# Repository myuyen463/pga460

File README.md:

# PGA460

Embedded platform for interfacing with Mega 2560 and multiple transducers

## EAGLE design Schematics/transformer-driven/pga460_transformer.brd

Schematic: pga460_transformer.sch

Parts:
5V/GND: FE05-2
B1: ARDUINO_MEGA_R3FULL; ARDUINO_MEGA_NO_SILK
C1, C2, C3, C6, C9, C12, C15, C16, C19: 0.1uF; C0805
C4, C10, C17: 100uF; C0805
C5, C11, C18: 680pF; C0805
C7, C13, C20: 390pF; C0805
C8, C14, C21: 0.033uF; C0805
D1, D2, D3: 1N4007; SMA
IC1, IC2, IC3: PGA460TPWQ1; SOP65P640X120-16N
MCP2515: CONN_07; 1X07
MURATA, MURATA1, MURATA2: ma59mf14-7n; 1X02
POWER: CONN_02; 1X02
R1, R9, R17: 10; R0805
R2, R3, R4, R10, R11, R12, R18, R19, R20: 10k; R0805
R5, R13, R21: 100; R0805
R6, R14, R22: 3k; R0805
R7, R15, R23: 3K; M0805
T1, T2, T3: B78416A2232A003
VIN: CONN_02; 1X02

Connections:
5V: 5V/GND.1, 5V/GND.3, 5V/GND.5, 5V/GND.7, 5V/GND.9, B1.5V, B1.5V@1 (5V), B1.5V@2 (5V), MCP2515.1, R2.1, R3.1, R10.1, R11.1, R18.1, R19.1
AVDD1: C2.2, IC1.16 (AVDD)
AVDD2: C12.2, IC2.16 (AVDD)
AVDD3: C19.2, IC3.16 (AVDD)
CS: B1.53 (53/!CS), MCP2515.3
GND: 5V/GND.2, 5V/GND.4, 5V/GND.6, 5V/GND.8, 5V/GND.10, B1.GND, B1.GND@1 (GND), B1.GND@3 (GND), B1.GND@4 (GND), C1.1, C2.1, C3.1, C4.1, C5.1, C6.1, C8.2, C9.1, C10.1, C11.1, C12.1, C14.2, C15.1, C16.1, C17.1, C18.1, C19.1, C21.2, IC1.1 (GND_1), IC1.4 (GND_2), IC1.6 (GNDP), IC2.1 (GND_1), IC2.4 (GND_2), IC2.6 (GNDP), IC3.1 (GND_1), IC3.4 (GND_2), IC3.6 (GNDP), MCP2515.2, MURATA.2, MURATA1.2, MURATA2.2, POWER.2, R4.1, R6.2, R12.1, R14.2, R20.1, R22.2, T1.6, T2.6, T3.6
INN_1: C8.1, IC1.3 (INN)
INN_2: C14.1, IC2.3 (INN)
INN_3: C21.1, IC3.3 (INN)
INP_1: C7.1, IC1.2 (INP)
INP_2: C13.1, IC2.2 (INP)
INP_3: C20.1, IC3.2 (INP)
INT: MCP2515.7
IOREG1: C3.2, IC1.14 (IOREG)
IOREG2: C9.2, IC2.14 (IOREG)
IOREG3: C16.2, IC3.14 (IOREG)
MISO: B1.50 (50/MISO), MCP2515.4
MOSI: B1.51 (51/MOSI), MCP2515.5
unnamed: C7.2, R7.1
unnamed: C13.2, R15.1
unnamed: C20.2, R23.1
OUTA_1: IC1.5 (OUTA), T1.1
OUTA_2: IC2.5 (OUTA), T2.1
OUTA_3: IC3.5 (OUTA), T3.1
OUTB_1: IC1.7 (OUTB), T1.3
OUTB_2: IC2.7 (OUTB), T2.3
OUTB_3: IC3.7 (OUTB), T3.3
RX1: B1.19 (19(RX1)), IC1.10 (TXD), R3.2
RX2: B1.17 (17(RX2)), IC2.10 (TXD), R11.2
RX3: B1.15 (15(RX3)), IC3.10 (TXD), R19.2
S1+: C5.2, MURATA.1, R6.1, R7.2, T1.4
S2+: C11.2, MURATA1.1, R14.1, R15.2, T2.4
S3+: C18.2, MURATA2.1, R22.1, R23.2, T3.4
SCLK: B1.52 (52/SCK), MCP2515.6
SCLK1: IC1.12 (SCLK), R4.2
SCLK2: IC2.12 (SCLK), R12.2
SCLK3: IC3.12 (SCLK), R20.2
TEST1: IC1.9 (TEST), R2.2
TEST2: IC2.9 (TEST), R10.2
TEST3: IC3.9 (TEST), R18.2
TX1: B1.18 (18(TX1)), IC1.11 (RXD)
TX2: B1.16 (16(TX2)), IC2.11 (RXD)
TX3: B1.14 (14(TX3)), IC3.11 (RXD)
VIN: B1.VIN, C1.2, C4.2, C6.2, C10.2, C15.2, C17.2, D1.A, D1.K (C), D2.A, D2.K (C), D3.A, D3.K (C), IC1.15 (VPWR), IC2.15 (VPWR), IC3.15 (VPWR), POWER.1, R1.1, R1.2, R5.1, R5.2, R9.1, R9.2, R13.1, R13.2, R17.1, R17.2, R21.1, R21.2, T1.2, T2.2, T3.2, VIN.1, VIN.2

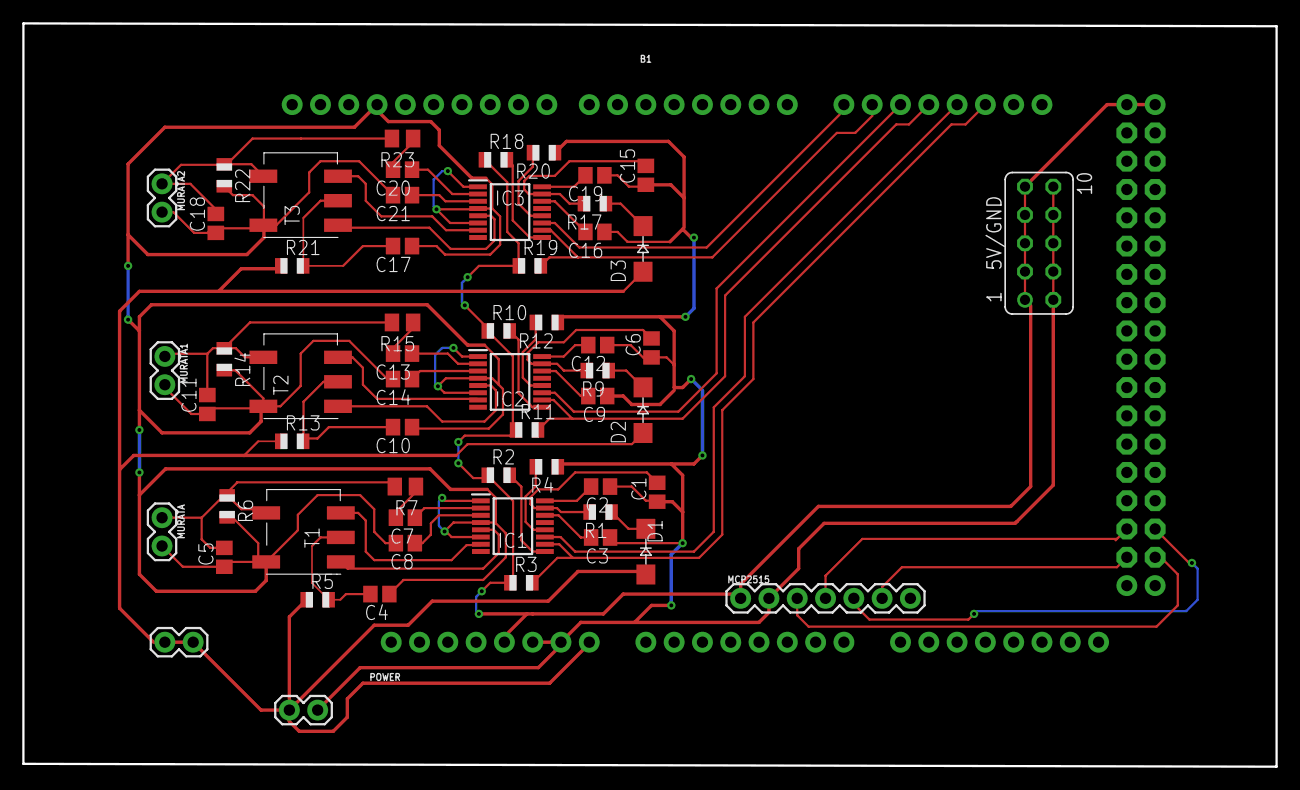
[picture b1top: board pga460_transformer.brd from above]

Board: 2 copper layers, 112.5 x 66.7 mm, 59 parts (0 on the bottom side), 43 nets.

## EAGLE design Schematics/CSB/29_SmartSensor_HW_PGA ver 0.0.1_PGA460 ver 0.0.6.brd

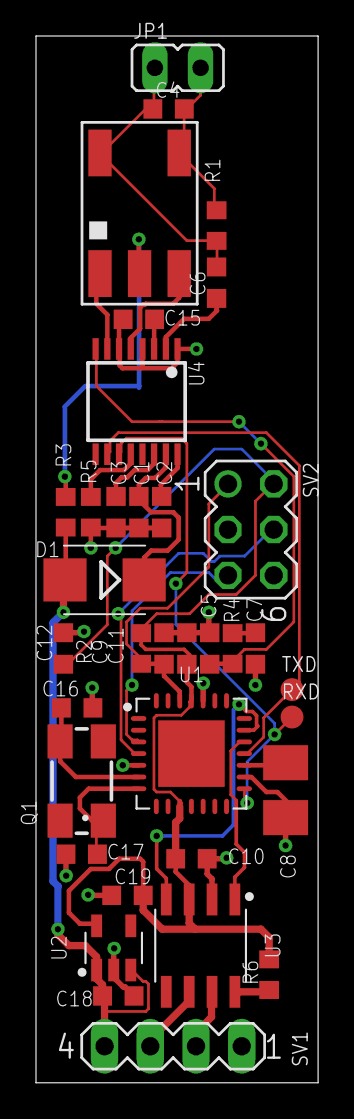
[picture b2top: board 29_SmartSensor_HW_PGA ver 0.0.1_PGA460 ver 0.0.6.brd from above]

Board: 2 copper layers, 15.7 x 58.2 mm, 36 parts (1 on the bottom side), 29 nets.

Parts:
C1, C2, C3, C9, C10, C11, C12, C18: 0.1uF; C0603K
C4: 1500pF; C0603K
C5, C7: 180pF; C0603K
C6: 390pF; C0603K
C8: 10uF/16V; B/3528-21R
C15: 0.033uF; C0603K
C16, C17: 18pF; C0603K
C19: 0.47uF; C0603K
C23: PANASONIC_D
D1: SS14FL; SMB
JP1: MA58MF14-7N; JP1
Q1: CTS406
R1: 2K7; R0603
R2, R6: 15K; R0603
R3, R4: 100E; R0603
R5: 10K; R0603
RXD: TXD; B1,27
SV1: MA04-1
SV2: MA03-2
T1: B78416
TXD: TXD; B1,27
U1: QFN65P600X600X100-29T370
U2: MIC5203; SOT95P280X110-5
U3: SOIC127P599X265-8
U4: PGA460; TSSOP16

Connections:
/MCLR: C9.1, R2.1, SV2.1, U1.26
CANH: SV1.2, U3.7
CANL: SV1.3, U3.6
CANRX: U1.20, U3.4
CANTX: U1.19, U3.1
GND: C1.2, C2.2, C3.2, C5.2, C7.2, C8.-, C9.2, C10.2, C11.2, C12.2, C15.2, C16.1, C17.1, C18.1, C19.1, C23.-, R5.1, SV1.1, SV2.3, U1.5, U1.16, U1.24, U2.2, U3.2, U4.1, U4.4, U4.6
ICSPCLK: SV2.5, U1.3
ICSPDAT: SV2.4, U1.4
INN: C15.1, U4.3
INP: C6.1, U4.2
IO: C5.1, R4.1, U4.8
unnamed: R5.2, U4.12
unnamed: R6.1, U3.8
unnamed: C23.+, R3.2, T1.2
unnamed: C3.1, U4.14
unnamed: C2.1, U4.16
unnamed: C4.1, C6.2, JP1.1, R1.2, T1.6
unnamed: C1.1, D1.C, U4.15
unnamed: C4.2, JP1.2, R1.1, T1.4
unnamed: C8.+, U1.17
OSC1: C16.2, Q1.3, U1.6
OSC2: C17.2, Q1.1, U1.7
OUTA: T1.3, U4.5
OUTB: T1.1, U4.7
TCI: C7.1, R4.2
UARTRX: TXD.TP, U1.18, U4.10
UARTTX: RXD.TP, U1.15, U4.11
VDD: C10.1, C11.1, C12.1, C19.2, R2.2, R6.2, SV2.2, U1.10, U1.25, U2.5, U3.3
VPWR: C18.2, D1.A, R3.1, SV1.4, U2.1, U2.3

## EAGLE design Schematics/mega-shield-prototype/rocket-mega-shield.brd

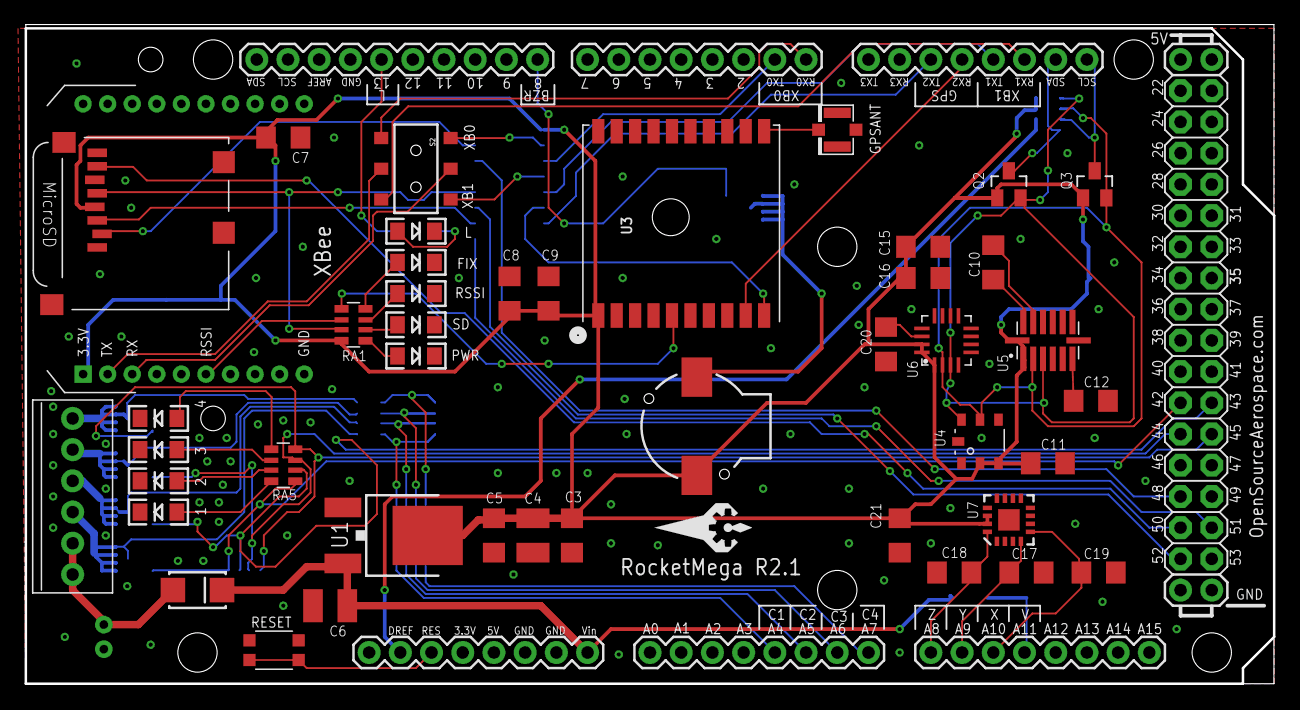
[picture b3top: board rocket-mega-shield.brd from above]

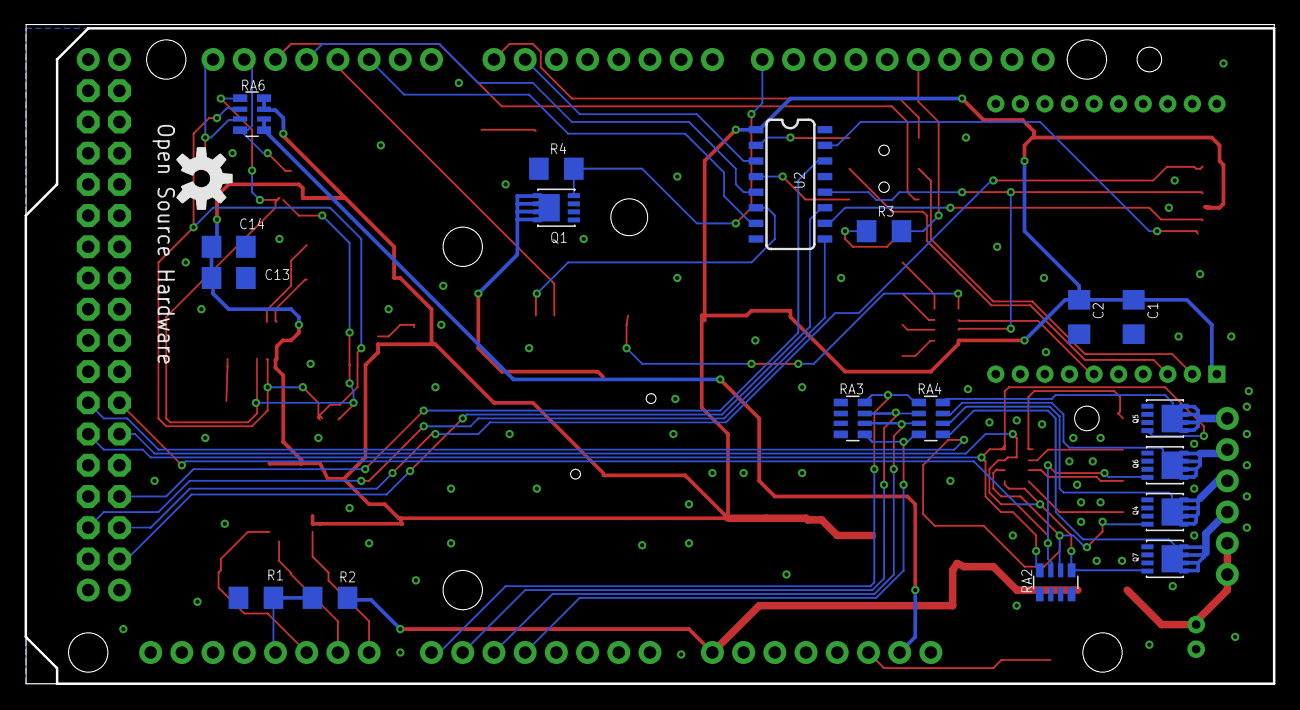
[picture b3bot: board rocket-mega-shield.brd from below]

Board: 2 copper layers, 101.6 x 53.6 mm, 66 parts (19 on the bottom side), 63 nets.

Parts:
C1, C5, C13, C15: 10uF; C1206
C2, C7, C11, C14, C16, C21: 0.1uF; C1206
C3: 100uF; C1206
C4: 220uF; C1210
C6: 100uF16V; C1210
C8: 1uF; C1206
C9, C17, C18, C19, C20: 0.01uF; C1206
C10: 0.22uF; C1206
C12: 4.7uF; C1206
D1: STTH102A; SMA-DIODE_ALT
D2: 13 - red; LED-1206
D3: Fix - blue; LED-1206
D4: RSSI - yellow; LED-1206
D5: SDAct - orange; LED-1206
D6: PWR - green; LED-1206
D7: Pyro1 - red; LED-1206
D8: Pyro2 - red; LED-1206
D9: Pyro3 - red; LED-1206
D10: Pyro4 - red; LED-1206
J1: ExtBatt; JST-2-PTH-NS
J2: Mega R3; ARDUINO_MEGA
J3: XBEE
J4: MICROSD
J5: U.FL
J6: 1X6TERMINALBLOCK
LOGO1: OSHW-LOGOM; OSHW-LOGO-M
Q1, Q4, Q5, Q6, Q7: SI7112DN; POWERPAK1212-8
Q2, Q3: BSS138; SOT23
R1: 100k; R1206
R2: 620k; R1206
R3: 330; R1206
R4: 10k; R1206
RA1, RA5: 330; 1206X4RESISTORARRAY
RA2, RA6: 10k; 1206X4RESISTORARRAY
RA3: 100k; 1206X4RESISTORARRAY
RA4: 620k; 1206X4RESISTORARRAY
S1: KMR2; TACTILE_KMR2
S2: AYZ0202
SG1: CCV084; BUZZER-CCV
U1: NCP1117DT33G; DPAK
U2: M74HC4050M; SO016
U3: FGPMMOPA6H
U4: BMP180
U5: LSM303DLHCTR; LGA14
U6: L3GD20TR; LGA16-4X4
U7: ADXL377; LFCSP-16
U$1: OSAEROSPACEVECTOR; OSAEROSPACE_V

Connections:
BATT+: D1.A, J1.2, J6.1, J6.2
GND: C1.2, C2.2, C3.2, C4.2, C5.2, C6.2, C7.2, C8.2, C9.2, C11.2, C12.2, C13.2, C14.2, C15.2, C16.2, C17.2, C18.2, C19.2, C20.2, C21.2, D2.C, D3.C, D4.C, D5.C, D6.C, D7.C, D8.C, D9.C, D10.C, J1.1, J2.GND@0, J2.GND@1, J2.GND@2, J2.GND@3, J2.GND@4, J3.10, J4.6, J4.CD1, J4.CD2, J4.MT1, J4.MT2, J5.P$1, J5.P$2, Q1.S1, Q1.S2, Q1.S3, Q4.S1, Q4.S2, Q4.S3, Q5.S1, Q5.S2, Q5.S3, Q6.S1, Q6.S2, Q6.S3, Q7.S1, Q7.S2, Q7.S3, R1.1, R4.2, RA2.5, RA2.6, RA2.7, RA2.8, RA3.1, RA3.2, RA3.3, RA3.4, S1.3, S1.4, U1.1, U2.8, U3.P$3, U3.P$8, U3.P$12, U3.P$19, U4.7, U5.7, U5.10, U5.11, U6.P$8, U6.P$9, U6.P$10, U6.P$11, U6.P$12, U6.P$13, U7.6, U7.7
GPSFIX: RA1.1, U3.P$5
IOREF: J2.IOREF, RA6.1, RA6.2
MEGA8: J2.8, Q1.G, R4.1
MEGAA4: J2.A4, RA3.5, RA4.4
MEGAA5: J2.A5, RA3.6, RA4.3
MEGAA6: J2.A6, RA3.7, RA4.2
MEGAA7: J2.A7, RA3.8, RA4.1
MEGAA8: C18.1, J2.A8, U7.16
MEGAA9: C17.1, J2.A9, U7.4
MEGAA10: C19.1, J2.A10, U7.5
MEGAA11: J2.A11, R1.2, R2.1
MEGAMISO: J2.50, J4.7
MEGAMOSI: J2.51, U2.9
MEGARX0: J2.0, S2.4
MEGARX1: J2.19, S2.6
MEGARX2: J2.17, U3.P$9
MEGASCL: J2.21, Q3.3, RA6.7
MEGASCLK: J2.52, U2.11
MEGASDA: J2.20, Q2.3, RA6.8
MEGASDCS: J2.48, U2.14
MEGATX0: J2.1, U2.3
MEGATX1: J2.18, U2.5
MEGATX2: J2.16, U2.7
MOSI: J4.3, U2.10
unnamed: D6.A, RA1.5
unnamed: D5.A, RA1.6
unnamed: J6.3, Q7.D1, Q7.D2, Q7.D3, Q7.D4, Q7.DPAD, RA4.5
unnamed: J6.4, Q4.D1, Q4.D2, Q4.D3, Q4.D4, Q4.DPAD, RA4.6
unnamed: C10.2, U5.12
unnamed: C10.1, U5.13
unnamed: C12.1, U5.6
unnamed: C20.1, U6.P$14
unnamed: J2.13, R3.1
unnamed: J5.P$3, U3.P$11
unnamed: D4.A, RA1.7
unnamed: D3.A, RA1.8
unnamed: Q1.D1, Q1.D2, Q1.D3, Q1.D4, Q1.DPAD, SG1.+
unnamed: D2.A, R3.2
unnamed: D10.A, RA5.5
unnamed: D9.A, RA5.6
unnamed: D8.A, RA5.7
unnamed: D7.A, RA5.8
unnamed: J3.2, S2.5
unnamed: J3.3, S2.2
unnamed: J6.6, Q5.D1, Q5.D2, Q5.D3, Q5.D4, Q5.DPAD, RA4.8
unnamed: J6.5, Q6.D1, Q6.D2, Q6.D3, Q6.D4, Q6.DPAD, RA4.7
PYRO1: J2.42, Q7.G, RA2.1, RA5.1
PYRO2: J2.43, Q4.G, RA2.2, RA5.2
PYRO3: J2.44, Q6.G, RA2.3, RA5.3
PYRO4: J2.45, Q5.G, RA2.4, RA5.4
RESET: J2.RESET, S1.1, S1.2
SCL: Q3.2, RA6.6, U4.5, U5.2, U6.P$2
SCLK: J4.5, RA1.3, U2.12
SDA: Q2.2, RA6.5, U4.6, U5.3, U6.P$3
SDCS: J4.2, U2.15
TX0: S2.1, U2.2
TX1: S2.3, U2.4
TX2: U2.6, U3.P$10
VCC3: C1.1, C2.1, C3.1, C4.1, C5.1, C7.1, C8.1, C9.1, C11.1, C13.1, C14.1, C15.1, C16.1, C21.1, J3.1, J4.4, Q2.1, Q3.1, RA1.4, RA6.3, RA6.4, SG1.-, U1.4, U2.1, U3.P$1, U4.2, U4.3, U5.1, U5.14, U6.P$1, U6.P$15, U6.P$16, U7.14, U7.15
VIN: C6.1, D1.C, J2.VIN, R2.2, U1.3
XRSSI: J3.6, RA1.2

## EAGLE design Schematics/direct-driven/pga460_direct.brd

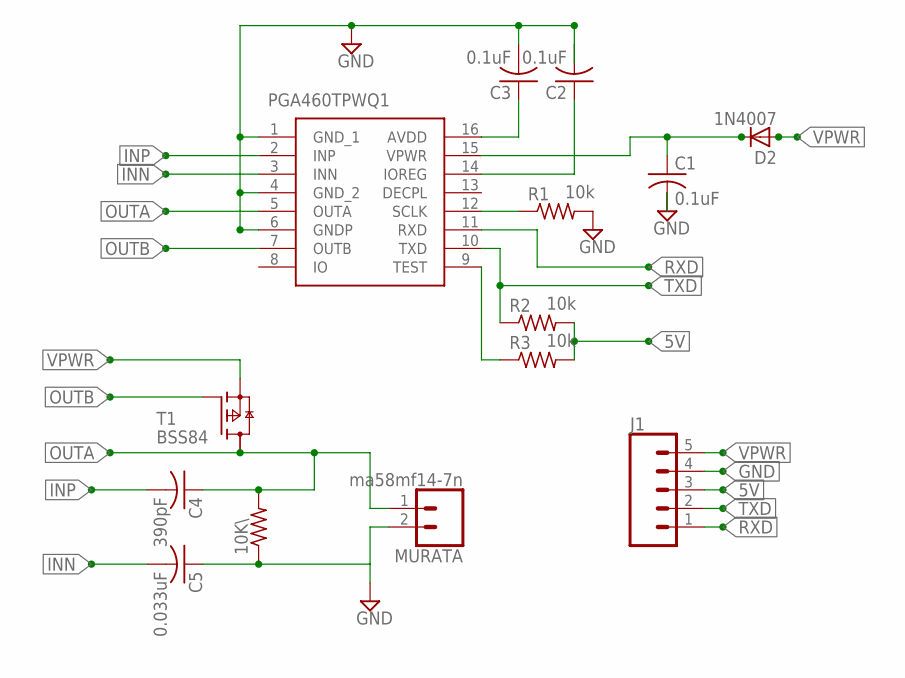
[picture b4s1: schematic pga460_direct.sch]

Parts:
10K\: R-US_M0805; M0805
C1, C2, C3: 0.1uF; C0805
C4: 390pF; C0805
C5: 0.033uF; C0805
D2: 1N4007; SMA
IC1: PGA460TPWQ1; SOP65P640X120-16N
J1: CONN_05; 1X05
MURATA: ma58mf14-7n; 1X02_LOCK
R1, R2, R3: 10k; R0805
T1: BSS84; SOT23

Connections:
5V: J1.3, R2.2, R3.2
GND: 10K\.1, C1.2, C2.2, C3.2, C5.1, IC1.1 (GND_1), IC1.4 (GND_2), IC1.6 (GNDP), J1.4, MURATA.2, R1.2
INN: C5.2, IC1.3 (INN)
INP: C4.2, IC1.2 (INP)
unnamed: IC1.12 (SCLK), R1.1
unnamed: C1.1, D2.K (C), IC1.15 (VPWR)
unnamed: C3.1, IC1.16 (AVDD)
unnamed: IC1.9 (TEST), R3.1
unnamed: C2.1, IC1.14 (IOREG)
OUTA: 10K\.2, C4.1, IC1.5 (OUTA), MURATA.1, T1.3 (D)
OUTB: IC1.7 (OUTB), T1.1 (G)
RXD: IC1.11 (RXD), J1.1
TXD: IC1.10 (TXD), J1.2, R2.1
VPWR: D2.A, J1.5, T1.2 (S)

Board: 2 copper layers, 14 parts (0 on the bottom side), 14 nets, no tracks yet.

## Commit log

2019-07-10 add all files
2019-07-10 add files currently developing
2019-07-11 modify c and ino file to assign different serial ports to different pgas
2019-07-11 modify ino file to accomodate multiple pgas
2019-07-15 Remove unnecessary code of other modes of communication
2019-07-15 add other schematics for transformer-driven
2019-07-16 add libraries for eagle
2019-07-16 fix 0x44 and 0x45 flickering due to not long enough delay for P2BL
2019-07-16 remove unnecessary Serial.print to enable faster cycle
2019-07-16 check for reliability of sensors
2019-07-19 Create test code running multiple pgas without using PGA460 library
2019-07-19 Add spreadsheet converting raw echo dump data to GUI readable format
2019-07-19 Reorganize all files into appropriate folders
2019-07-19 Export direct-driven schematics
2019-07-19 Add new libraries to EAGLE
2019-07-19 Add files of collected echo data dump
2019-07-19 Update progress report
2019-07-22 Create pcb board for transformer-driven
2019-07-23 Start writing troubleshooting guide for progress report
2019-07-26 CAN transmitting and receiving code created
2019-07-26 Add CAN com to GetDistance
2019-07-26 Tmeplate added
2019-07-29 CAN bus
2019-07-29 Convert int to 2 bytes, 2 bytes to int
2019-07-29 Generating random distance to transmit on CAN Bus
2019-07-29 stimulate 4 random distances. 21 fps
2019-07-30 Ensure 8Mhz crystal parameter encoded
2019-07-30 replace receiving code
2019-07-30 remove non-wroking transmitting code
2019-07-30 replace with working transmitting code
2019-07-30 rename
2019-07-31 Change last distance to frame counter to keep track of full data transmission
2019-07-31 Add sub comm serial parser
2019-07-31 Remove shortening
2019-08-05 Update report
2019-08-08 Update parameters for transformer-driven
2019-08-09 successful 2-sensors setup
2019-08-09 successful 3-sensors setup
2019-08-09 fps 30 max for 3-sensor setup
2019-08-10 Verify feed rate: 1 sensor: 50, 2: 44, 3: 30
2019-08-10 CAN integrated
2019-08-12 update report. add in mega shield template.
2019-08-12 flexible numSerial success. integrate CAN comm
2019-08-12 update layout for transformer-driven
2019-08-12 update layout
2019-08-12 reorganize repository
2019-08-13 change track width
2019-08-13 change connector package
2019-08-13 Revert "change pga460"
    This reverts commit 5526e345e05617587ab5371b9eea014fc9cbd72d
2019-08-13 Revert "change pga460"
    This reverts commit 11281d79b47b0006704001165f10d30d9cd033b8
2019-08-13 change pga460
2019-08-13 move track to avoid crossing
2019-08-13 reorganize repo. update report
2019-08-13 add datasheets
2019-08-13 add presentation template
2019-08-13 update presentation
2019-08-14 update ppt
2019-08-14 finalize ppt
2019-08-14 solder PCB and match software
2019-08-30 Transfer to personal github account
2019-08-30 Prevent smaller gaps between tracks

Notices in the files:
parts and their libraries:
SparkFun-Connectors: Licensing: Creative Commons ShareAlike 4.0 International - https://creativecommons.org/licenses/by-sa/4.0
SparkFun-Connectors: Licensing: CC v3.0 Share-Alike You are welcome to use this library for commercial purposes.
